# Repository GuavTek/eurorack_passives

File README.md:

Various passive utility modules for eurorack. All modules are 1u height.
Renders of schematics and layouts, as well as any notes about problems, [can be viewed on CADLAB](https://cadlab.io/project/28283/main/files)

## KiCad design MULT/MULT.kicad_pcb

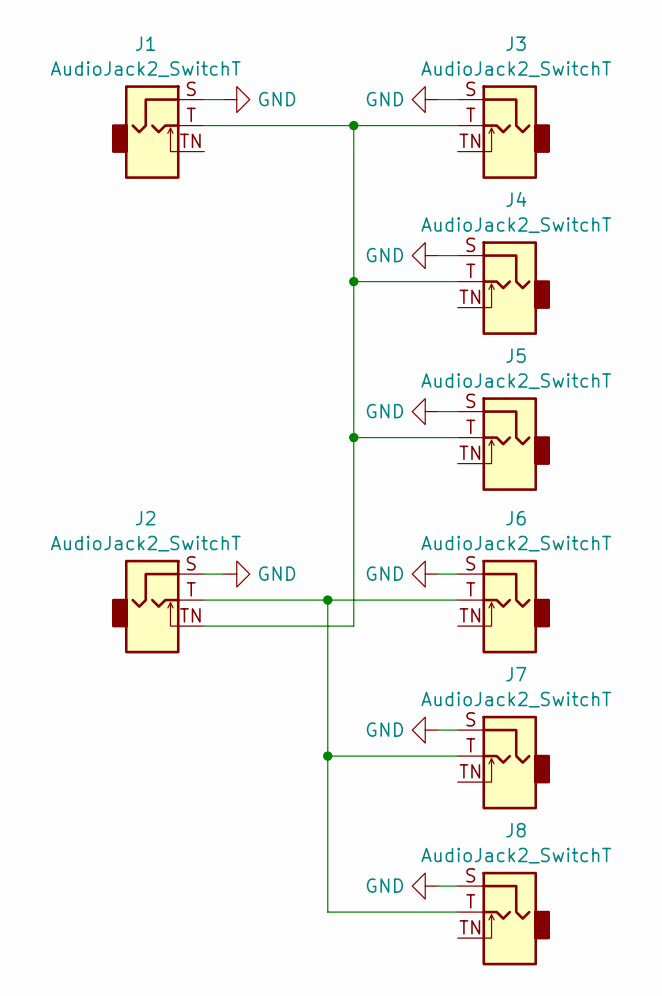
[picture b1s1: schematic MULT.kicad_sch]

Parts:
J1, J2, J3, J4, J5, J6, J7, J8: AudioJack2_SwitchT; PJ398SM

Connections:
GND: J1.S, J2.S, J3.S, J4.S, J5.S, J6.S, J7.S, J8.S
unnamed: J1.T, J2.TN, J3.T, J4.T, J5.T
unnamed: J2.T, J6.T, J7.T, J8.T

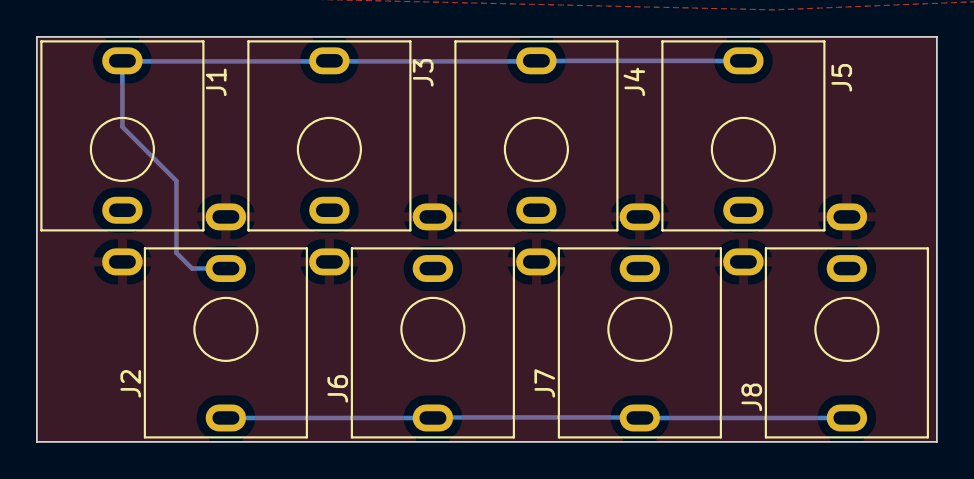
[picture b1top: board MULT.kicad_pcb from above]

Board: 2 copper layers, 50.0 x 22.5 mm, 8 parts (0 on the bottom side), 3 nets.

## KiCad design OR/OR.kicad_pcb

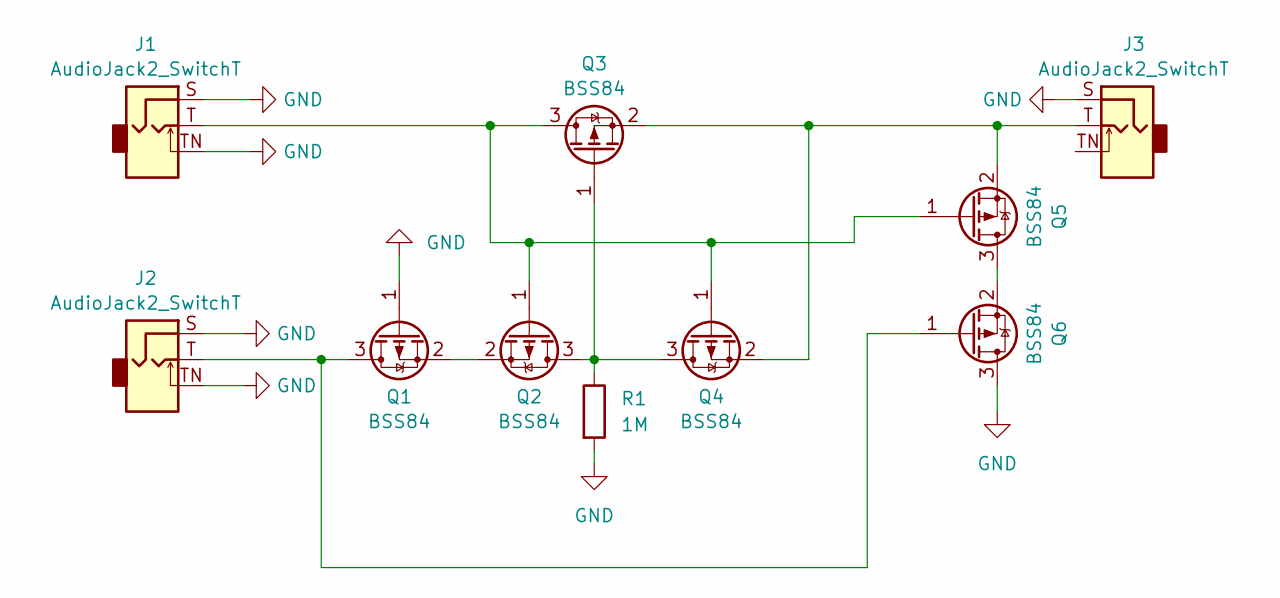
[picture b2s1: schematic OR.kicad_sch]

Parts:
J1, J2, J3: AudioJack2_SwitchT; PJ398SM
Q1, Q2, Q3, Q4, Q5, Q6: BSS84; SOT-23
R1: 1M; R_0603_1608Metric

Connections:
GND: J1.S, J1.TN, J2.S, J2.TN, J3.S, Q1.1 (G), Q6.3 (D), R1.2
unnamed: J2.T, Q1.3 (D), Q6.1 (G)
unnamed: Q1.2 (S), Q2.2 (S)
unnamed: Q2.3 (D), Q3.1 (G), Q4.3 (D), R1.1
unnamed: J1.T, Q2.1 (G), Q3.3 (D), Q4.1 (G), Q5.1 (G)
unnamed: J3.T, Q3.2 (S), Q4.2 (S), Q5.2 (S)
unnamed: Q5.3 (D), Q6.2 (S)

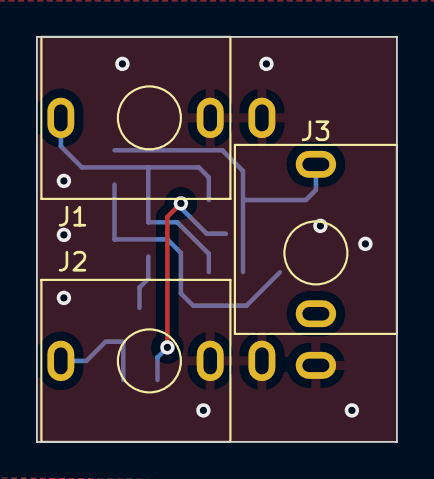
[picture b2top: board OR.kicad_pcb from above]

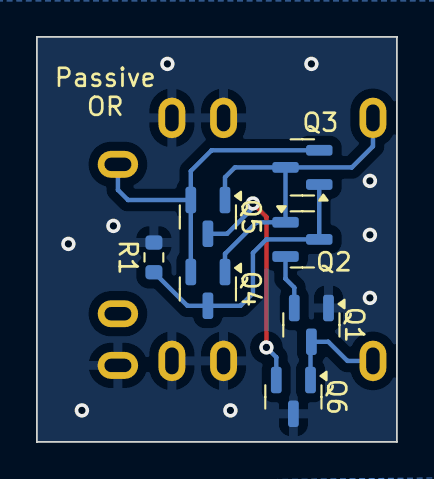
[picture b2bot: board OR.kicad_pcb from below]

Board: 2 copper layers, 20.0 x 22.5 mm, 10 parts (7 on the bottom side), 7 nets.

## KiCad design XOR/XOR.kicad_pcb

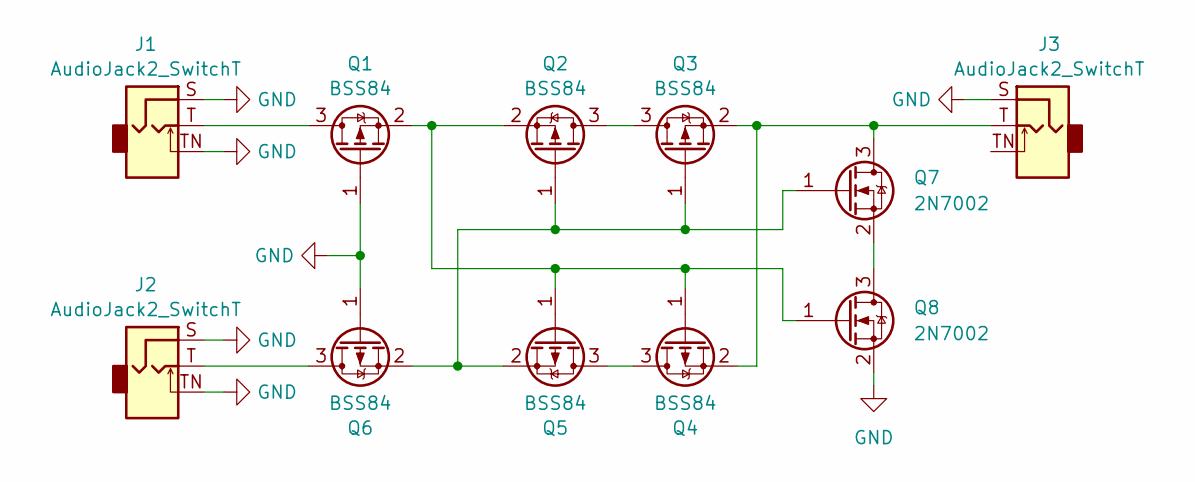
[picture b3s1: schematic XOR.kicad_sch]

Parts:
J1, J2, J3: AudioJack2_SwitchT; PJ398SM
Q1, Q2, Q3, Q4, Q5, Q6: BSS84; SOT-23
Q7, Q8: 2N7002; SOT-23

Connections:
GND: J1.S, J1.TN, J2.S, J2.TN, J3.S, Q1.1 (G), Q6.1 (G), Q8.2 (S)
unnamed: J1.T, Q1.3 (D)
unnamed: Q1.2 (S), Q2.2 (S), Q4.1 (G), Q5.1 (G), Q8.1 (G)
unnamed: Q2.3 (D), Q3.3 (D)
unnamed: Q2.1 (G), Q3.1 (G), Q5.2 (S), Q6.2 (S), Q7.1 (G)
unnamed: J3.T, Q3.2 (S), Q4.2 (S), Q7.3 (D)
unnamed: Q4.3 (D), Q5.3 (D)
unnamed: J2.T, Q6.3 (D)
unnamed: Q7.2 (S), Q8.3 (D)

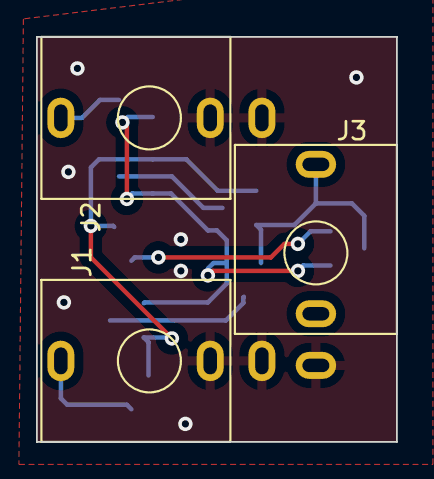
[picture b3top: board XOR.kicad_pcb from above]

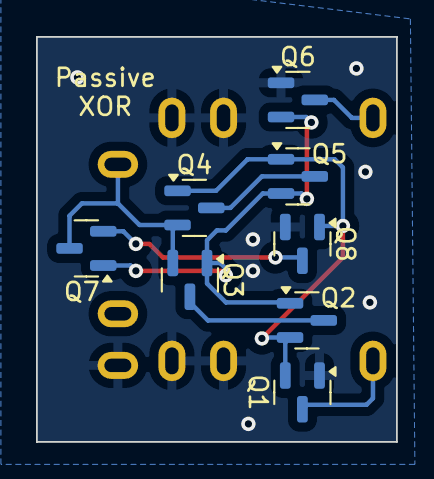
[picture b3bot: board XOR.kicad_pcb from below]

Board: 2 copper layers, 20.0 x 22.5 mm, 11 parts (8 on the bottom side), 9 nets.

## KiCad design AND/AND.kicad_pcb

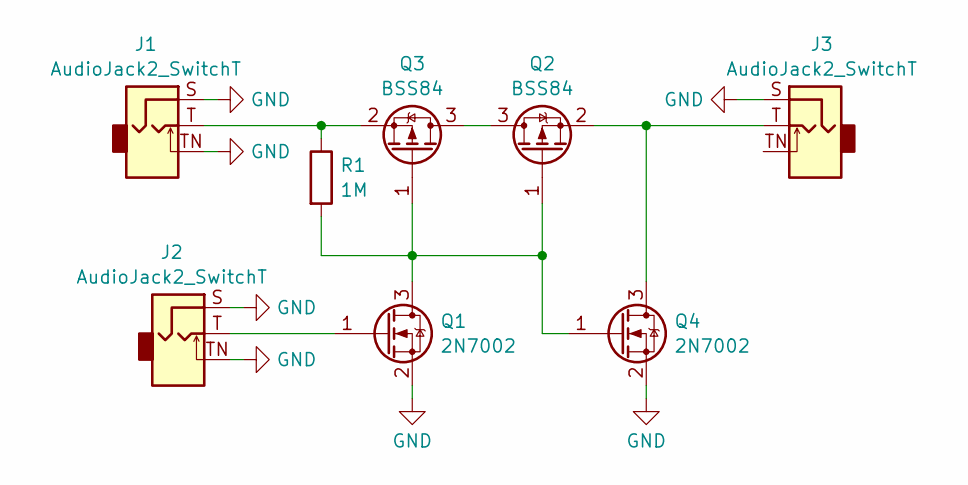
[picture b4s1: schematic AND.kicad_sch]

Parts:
J1, J2, J3: AudioJack2_SwitchT; PJ398SM
Q1, Q4: 2N7002; SOT-23
Q2, Q3: BSS84; SOT-23
R1: 1M; R_0603_1608Metric

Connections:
GND: J1.S, J1.TN, J2.S, J2.TN, J3.S, Q1.2 (S), Q4.2 (S)
unnamed: Q1.3 (D), Q2.1 (G), Q3.1 (G), Q4.1 (G), R1.2
unnamed: J2.T, Q1.1 (G)
unnamed: Q2.3 (D), Q3.3 (D)
unnamed: J3.T, Q2.2 (S), Q4.3 (D)
unnamed: J1.T, Q3.2 (S), R1.1

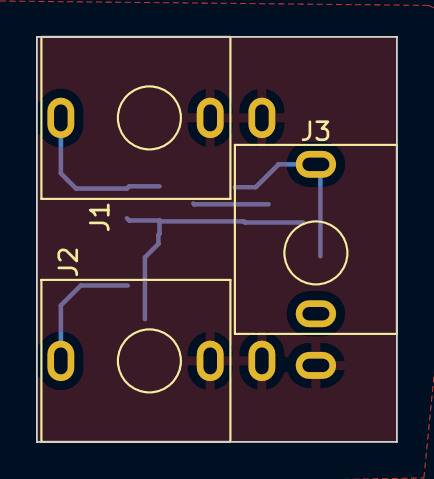
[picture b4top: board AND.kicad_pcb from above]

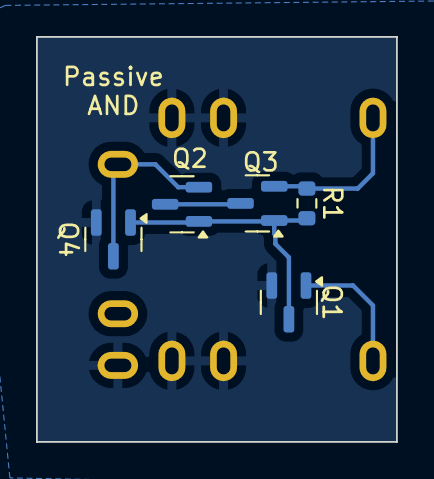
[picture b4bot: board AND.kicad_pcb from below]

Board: 2 copper layers, 20.0 x 22.5 mm, 8 parts (5 on the bottom side), 6 nets.

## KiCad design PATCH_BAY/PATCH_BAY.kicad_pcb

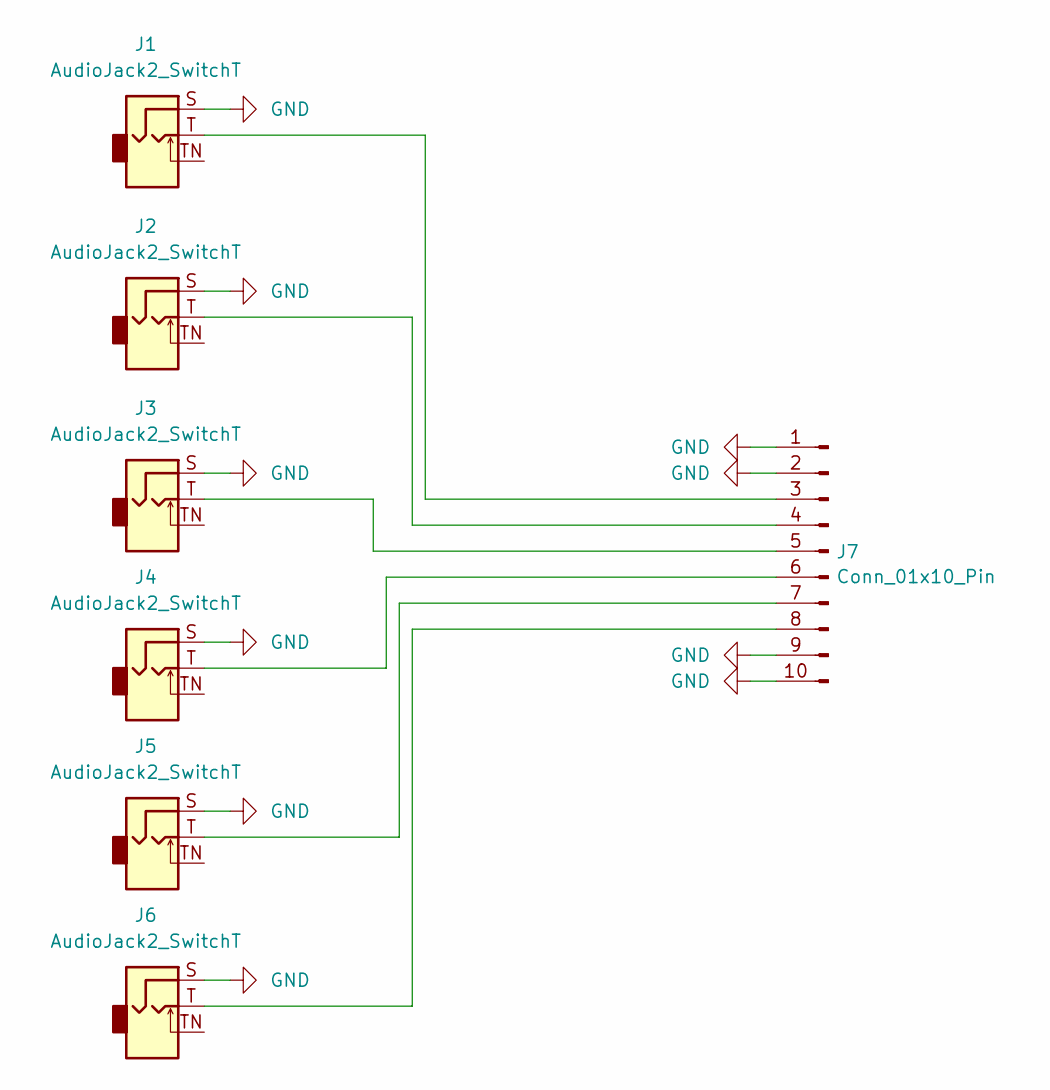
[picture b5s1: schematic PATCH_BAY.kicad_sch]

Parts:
J1, J2, J3, J4, J5, J6: AudioJack2_SwitchT; PJ398SM
J7: Conn_01x10_Pin; PinHeader_2x05_P2.54mm_Vertical_SMD

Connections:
GND: J1.S, J2.S, J3.S, J4.S, J5.S, J6.S, J7.1, J7.2, J7.9, J7.10
unnamed: J1.T, J7.3
unnamed: J2.T, J7.4
unnamed: J3.T, J7.5
unnamed: J4.T, J7.6
unnamed: J5.T, J7.7
unnamed: J6.T, J7.8

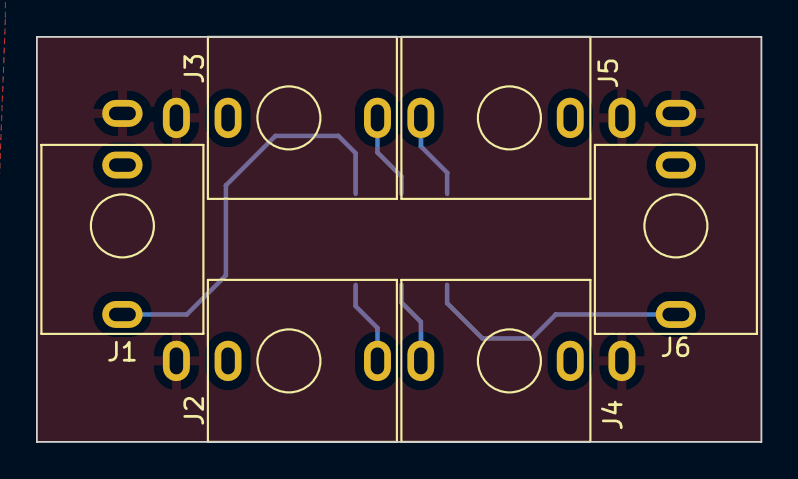
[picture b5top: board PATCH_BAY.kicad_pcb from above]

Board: 2 copper layers, 40.2 x 22.5 mm, 7 parts (1 on the bottom side), 7 nets.

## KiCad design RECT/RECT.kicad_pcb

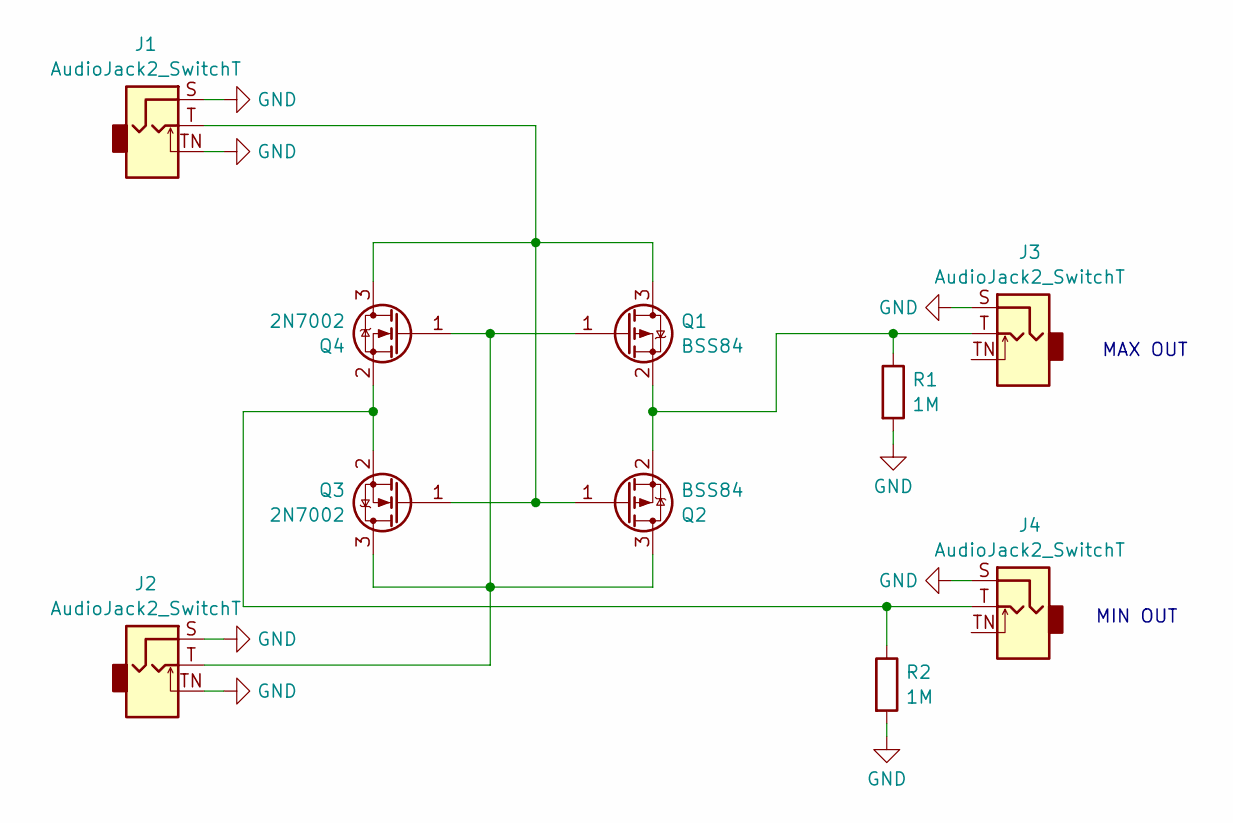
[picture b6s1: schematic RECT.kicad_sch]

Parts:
J1, J2, J3, J4: AudioJack2_SwitchT; PJ398SM
Q1, Q2: BSS84; SOT-23
Q3, Q4: 2N7002; SOT-23
R1, R2: 1M; R_0603_1608Metric

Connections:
GND: J1.S, J1.TN, J2.S, J2.TN, J3.S, J4.S, R1.2, R2.2
unnamed: J1.T, Q1.3 (D), Q2.1 (G), Q3.1 (G), Q4.3 (D)
unnamed: J2.T, Q1.1 (G), Q2.3 (D), Q3.3 (D), Q4.1 (G)
unnamed: J3.T, Q1.2 (S), Q2.2 (S), R1.1
unnamed: J4.T, Q3.2 (S), Q4.2 (S), R2.1

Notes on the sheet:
MAX OUT
MIN OUT

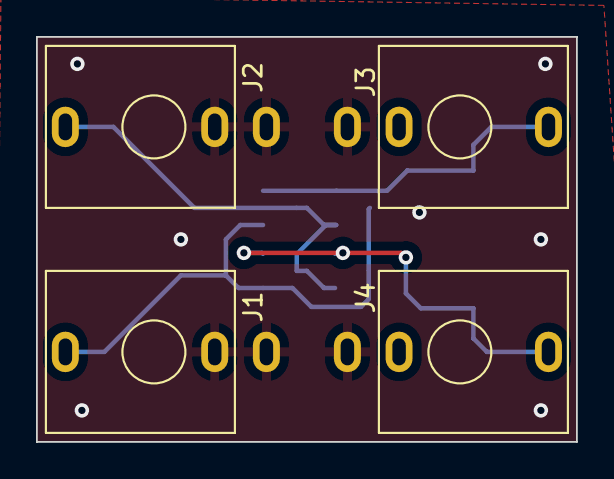
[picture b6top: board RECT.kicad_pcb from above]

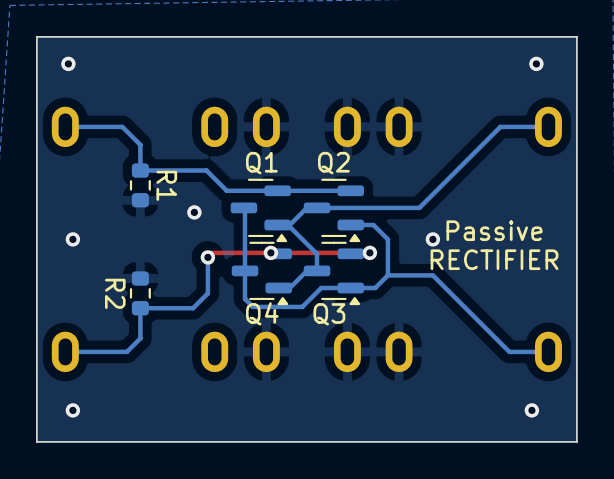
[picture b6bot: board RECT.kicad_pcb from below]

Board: 2 copper layers, 30.0 x 22.5 mm, 10 parts (6 on the bottom side), 5 nets.

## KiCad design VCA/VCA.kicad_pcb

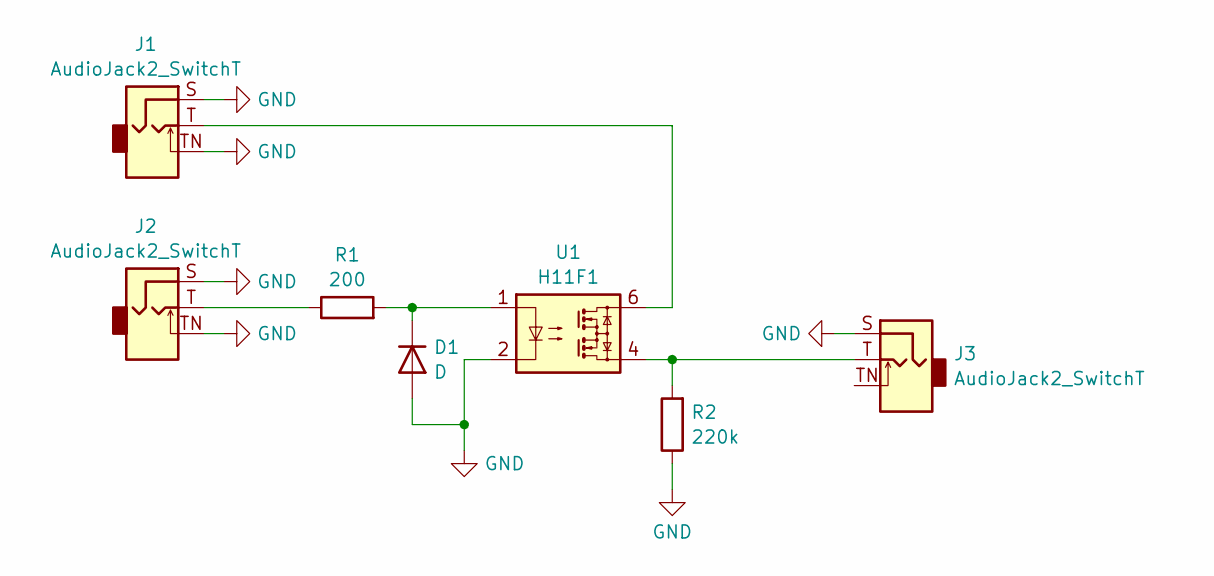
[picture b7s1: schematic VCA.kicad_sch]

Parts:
D1: D; D_SOD-323_HandSoldering
J1, J2, J3: AudioJack2_SwitchT; PJ398SM
R1: 200; R_0603_1608Metric
R2: 220k; R_0603_1608Metric
U1: H11F1; DIP-6_W8.89mm_SMDSocket_LongPads

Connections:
GND: D1.2 (A), J1.S, J1.TN, J2.S, J2.TN, J3.S, R2.1, U1.2
unnamed: D1.1 (K), R1.2, U1.1
unnamed: J1.T, U1.6
unnamed: J2.T, R1.1
unnamed: J3.T, R2.2, U1.4

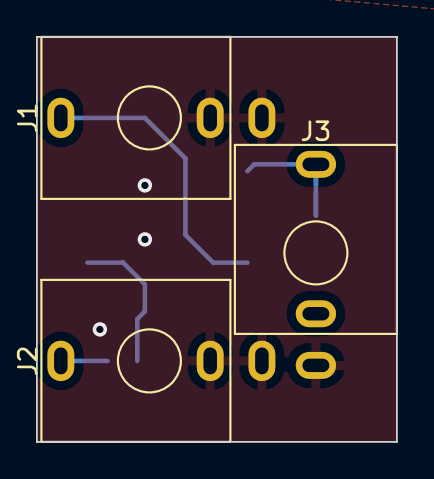
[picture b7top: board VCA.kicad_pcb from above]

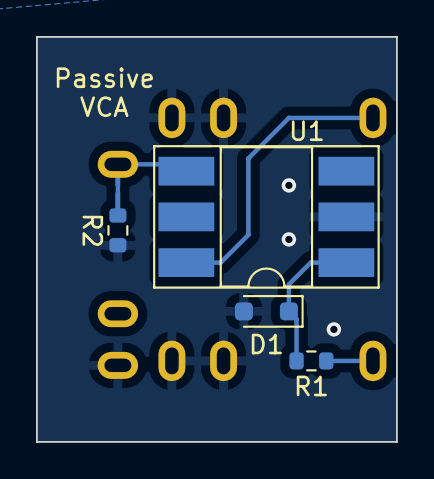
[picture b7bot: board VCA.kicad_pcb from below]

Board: 2 copper layers, 20.0 x 22.5 mm, 7 parts (4 on the bottom side), 5 nets.

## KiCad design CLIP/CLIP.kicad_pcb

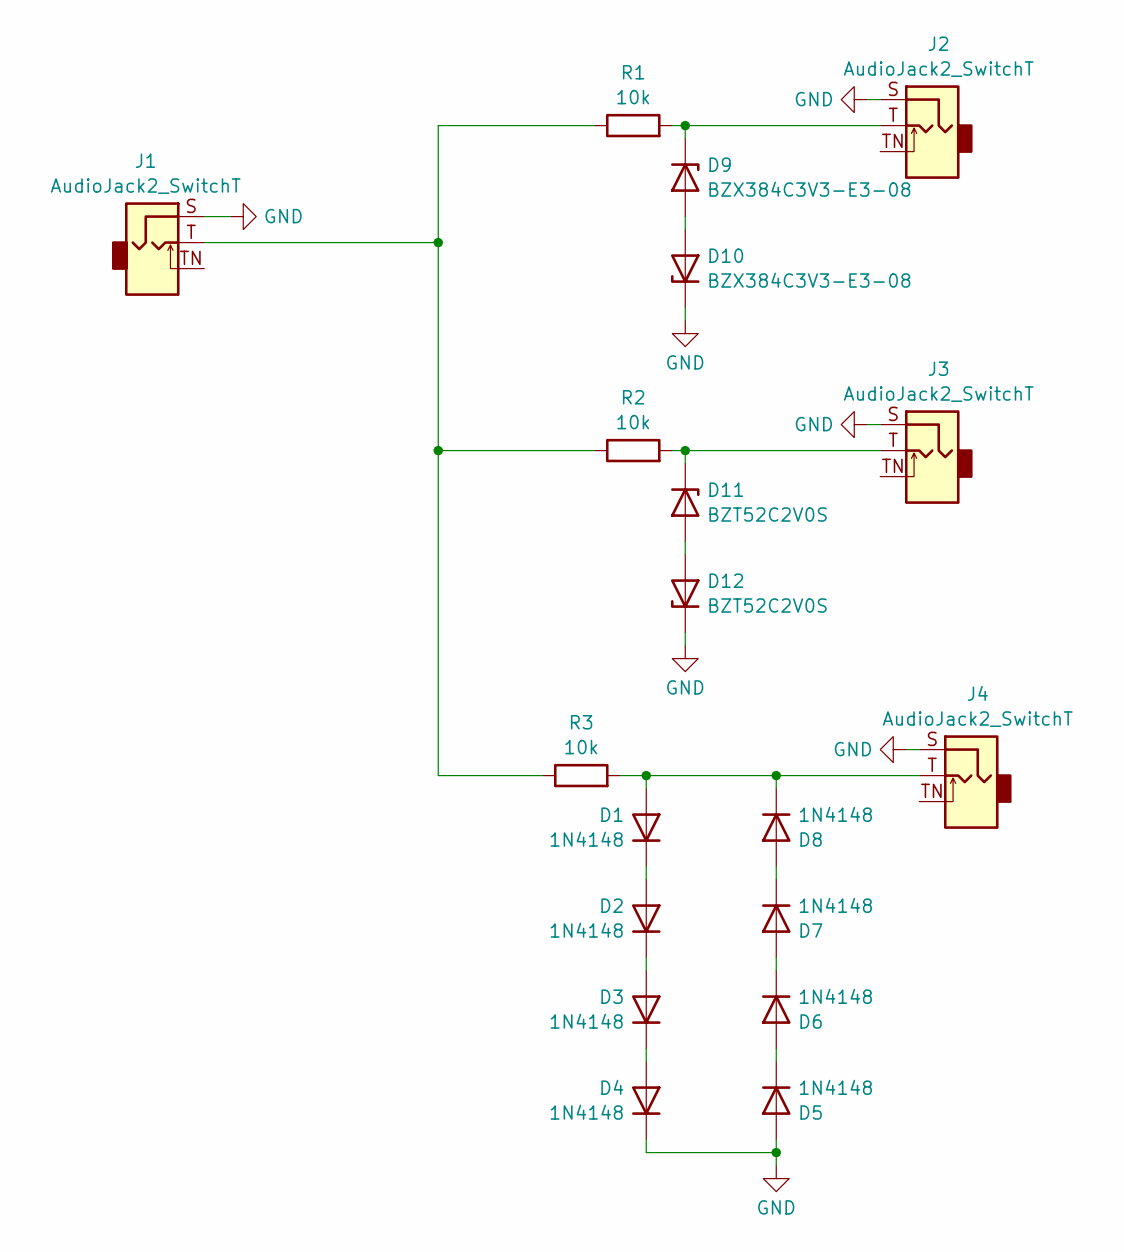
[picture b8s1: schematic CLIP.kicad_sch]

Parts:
D1, D2, D3, D4, D5, D6, D7, D8: 1N4148; D_SOD-323_HandSoldering
D9, D10: BZX384C3V3-E3-08; D_SOD-323_HandSoldering
D11, D12: BZT52C2V0S; D_SOD-323_HandSoldering
J1, J2, J3, J4: AudioJack2_SwitchT; PJ398SM
R1, R2, R3: 10k; R_0603_1608Metric

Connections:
GND: D4.1 (K), D5.2 (A), D10.1 (K), D12.1 (K), J1.S, J2.S, J3.S, J4.S
unnamed: D1.2 (A), D8.1 (K), J4.T, R3.2
unnamed: D1.1 (K), D2.2 (A)
unnamed: D2.1 (K), D3.2 (A)
unnamed: D3.1 (K), D4.2 (A)
unnamed: D5.1 (K), D6.2 (A)
unnamed: D6.1 (K), D7.2 (A)
unnamed: D7.1 (K), D8.2 (A)
unnamed: D9.1 (K), J2.T, R1.2
unnamed: D9.2 (A), D10.2 (A)
unnamed: D11.2 (A), D12.2 (A)
unnamed: D11.1 (K), J3.T, R2.2
unnamed: J1.T, R1.1, R2.1, R3.1
